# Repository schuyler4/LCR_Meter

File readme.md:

<h3> LCR Meter </h3>
<p>
 This is my attempt at making an LCR meter. It is still in progress, but here is a schematic if you are interested.
</p>
</img>
</img>

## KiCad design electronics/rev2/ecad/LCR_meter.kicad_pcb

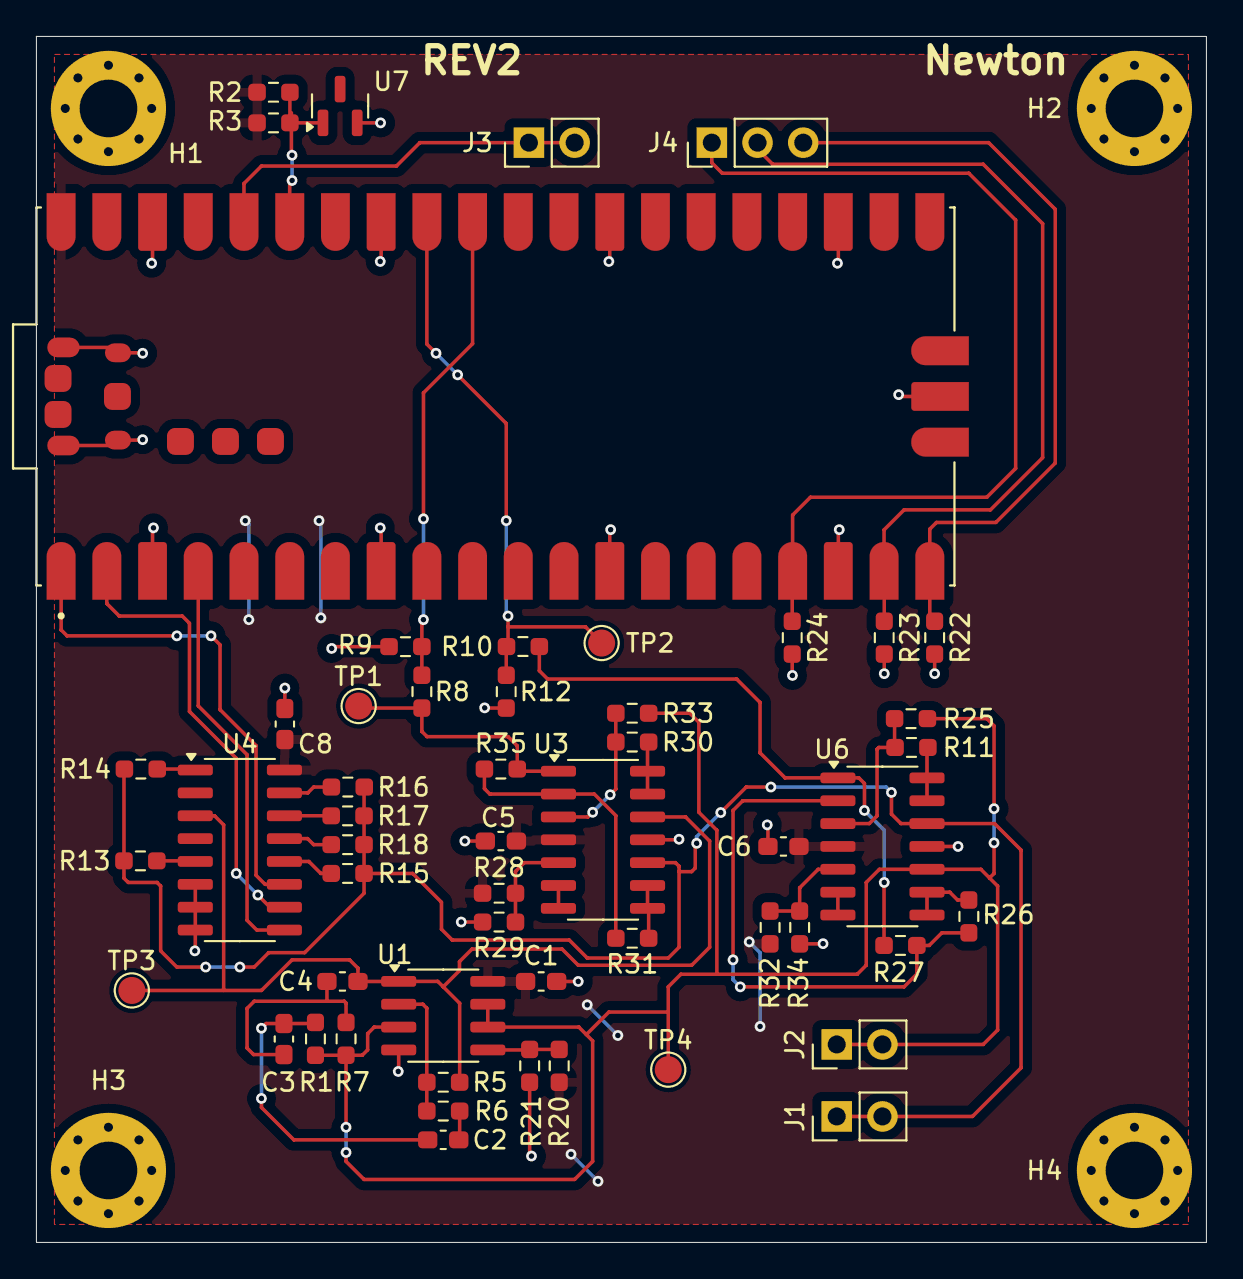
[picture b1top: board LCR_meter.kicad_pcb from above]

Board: 2 copper layers, 65.0 x 67.0 mm, 58 parts (0 on the bottom side), 40 nets.

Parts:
C1, C5, C6, C8: 0.1uF; C_0603_1608Metric_Pad1.08x0.95mm_HandSolder
C2, C3, C4: 100pF; C_0603_1608Metric_Pad1.08x0.95mm_HandSolder
H1, H2, H3, H4: M3; MountingHole_3.2mm_M3_Pad_Via
J1, J2: DUT; PinHeader_1x02_P2.54mm_Vertical
J3: SWITCH; PinHeader_1x02_P2.54mm_Vertical
J4: INPUT SWITCH; PinHeader_1x03_P2.54mm_Vertical
R1, R6, R7: 6.49k+/-0.1%; R_0603_1608Metric_Pad0.98x0.95mm_HandSolder
R2, R3, R22, R23, R24, R28, R29, R32, R34: 10k; R_0603_1608Metric_Pad0.98x0.95mm_HandSolder
R5: 249k+/-0.1%; R_0603_1608Metric_Pad0.98x0.95mm_HandSolder
R8, R10: 6.81k+/-0.1%; R_0603_1608Metric_Pad0.98x0.95mm_HandSolder
R9, R11, R12, R20, R21, R25, R26, R27, R30, R31, R33, R35: 10k+/-0.1%; R_0603_1608Metric_Pad0.98x0.95mm_HandSolder
R13: 49.9M+/-0.1%; R_0603_1608Metric_Pad0.98x0.95mm_HandSolder
R14: 4.99M+/-0.1%; R_0603_1608Metric_Pad0.98x0.95mm_HandSolder
R15: 499k+/-0.1%; R_0603_1608Metric_Pad0.98x0.95mm_HandSolder
R16: 49.9k+/-0.1%; R_0603_1608Metric_Pad0.98x0.95mm_HandSolder
R17: 4.99k+/-0.1%; R_0603_1608Metric_Pad0.98x0.95mm_HandSolder
R18: 499+/-0.1%; R_0603_1608Metric_Pad0.98x0.95mm_HandSolder
TP1, TP2, TP3, TP4: TestPoint_Pad_D1.5mm
U1: MCP6002-xSN; SOIC-8_3.9x4.9mm_P1.27mm
U3, U6: LM6144xIx; SOIC-14_3.9x8.7mm_P1.27mm
U4: 74HC4051; SOIC-16_3.9x9.9mm_P1.27mm
U5: SC0915; MODULE_SC0915
U7: LM4040DBZ-3; SOT-23

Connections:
+3.3V: J3.1, J3.2, U5.36 (3V3_OUT)
+5V: C1.1, C5.1, C6.1, C8.2, R2.1, R3.1, R20.1, R28.1, R32.1, U1.8 (V+), U3.4 (V+), U4.16 (VCC), U5.40 (VBUS), U6.4 (V+)
/DiffAmp1/IN+: C4.2, R5.2, TP3.1, U1.1, U3.12 (+), U4.3 (A)
/DiffAmp1/IN-: J1.1, J1.2, R13.2, R14.2, R15.2, R16.2, R17.2, R18.2, U3.10 (+), U6.12 (+)
/DiffAmp1/OUT: R8.2, R35.2, TP1.1, U3.1
/DiffAmp1/REF: J2.1, J2.2, R1.2, R7.2, R25.1, R33.1, TP4.1, U1.3 (+), U1.6 (-), U1.7, U6.10 (+)
/DiffAmp2/OUT: R10.2, R27.2, U6.1
/bit0: U4.11 (S0), U5.1 (GP0)
/bit1: U4.10 (S1), U5.2 (GP1)
/bit2: U4.9 (S2), U5.4 (GP2)
GND: C1.2, C5.2, C6.2, C8.1, H1.1, H2.1, H3.1, H4.1, R9.1, R12.2, R21.2, R22.2, R23.2, R24.2, R29.2, R34.2, U1.4 (V-), U3.11 (V-), U4.6 (~E), U4.7 (VEE), U4.8 (GND), U5.3 (GND), U5.8 (GND), U5.13 (GND), U5.18 (GND), U5.23 (GND), U5.28 (GND), U5.33 (AGND), U5.38 (GND), U5.A (USB_SHIELD), U5.B (USB_SHIELD), U5.C (USB_SHIELD), U5.D (USB_SHIELD), U5.D2 (GND), U6.11 (V-), U7.2 (A)
unnamed: C2.1, R6.2
unnamed: C2.2, C3.1, R1.1
unnamed: C3.2, C4.1, R7.1
unnamed: J4.1, R24.1, U5.17 (GP13)
unnamed: J4.2, R23.1, U5.19 (GP14)
unnamed: J4.3, R22.1, U5.20 (GP15)
unnamed: R5.1, R6.1, U1.2 (-)
unnamed: R20.2, R21.1, U1.5 (+)
unnamed: R30.2, R33.2, U3.3 (+)
unnamed: R31.2, R35.1, U3.2 (-)
unnamed: R28.2, R29.1, U3.5 (+)
unnamed: U3.6 (-), U3.7
unnamed: R31.1, U3.8, U3.9 (-)
unnamed: R30.1, U3.13 (-), U3.14
unnamed: R18.1, U4.13 (A0)
unnamed: R17.1, U4.14 (A1)
unnamed: R16.1, U4.15 (A2)
unnamed: R15.1, U4.12 (A3)
unnamed: R14.1, U4.1 (A4)
unnamed: R13.1, U4.5 (A5)
unnamed: R2.2, R3.2, U5.35 (ADC_VREF), U7.1 (K)
unnamed: R8.1, R9.2, U5.31 (GP26)
unnamed: R10.1, R12.1, TP2.1, U5.32 (GP27)
unnamed: R11.2, R25.2, U6.3 (+)
unnamed: R26.2, R27.1, U6.2 (-)
unnamed: R32.2, R34.1, U6.5 (+)
unnamed: U6.6 (-), U6.7
unnamed: R26.1, U6.8, U6.9 (-)
unnamed: R11.1, U6.13 (-), U6.14

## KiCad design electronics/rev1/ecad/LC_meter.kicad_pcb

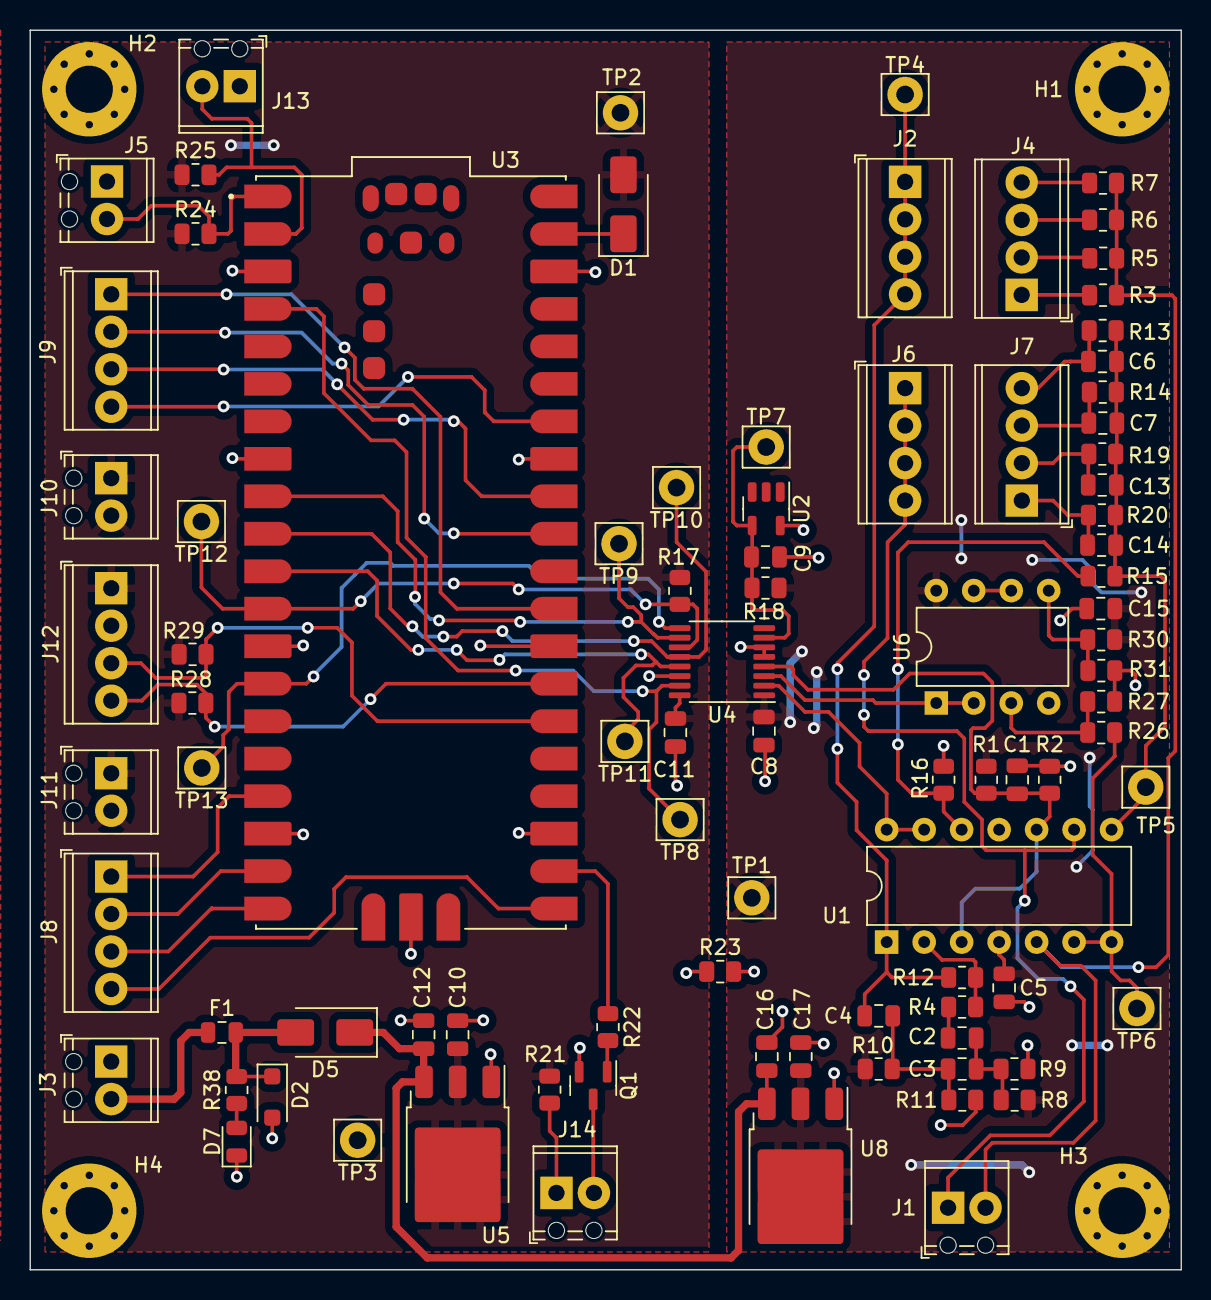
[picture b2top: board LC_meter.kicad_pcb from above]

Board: 2 copper layers, 78.0 x 84.0 mm, 93 parts (0 on the bottom side), 56 nets.

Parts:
C1, C5, C8, C11, C15, C16: 0.1uF; C_0805_2012Metric
C2, C3, C4: 100pF; C_0805_2012Metric
C6, C7, C13, C14: PNU; C_0805_2012Metric
C9, C10, C12, C17: 10uF; C_0805_2012Metric
D1, D5: B140-13-F; D_SMA
D2: SMF13A; D_SOD-123F
D7: LTST-C171TBKT; LED_0805_2012Metric
F1: 2A; Fuse_0805_2012Metric
H1, H2, H3, H4: M3; MountingHole_3.2mm_M3_Pad_Via
J1: DUT; TerminalBlock_Phoenix_MPT-0,5-2-2.54_1x02_P2.54mm_Horizontal
J2, J4, J6, J7: Switch; TerminalBlock_Phoenix_MPT-0,5-4-2.54_1x04_P2.54mm_Horizontal
J3: 12V Power; TerminalBlock_Phoenix_MPT-0,5-2-2.54_1x02_P2.54mm_Horizontal
J5, J13: Mode Switch; TerminalBlock_Phoenix_MPT-0,5-2-2.54_1x02_P2.54mm_Horizontal
J8: Thevenin Range Switch Indicator; TerminalBlock_Phoenix_MPT-0,5-4-2.54_1x04_P2.54mm_Horizontal
J9: Current Range Switch Indicator; TerminalBlock_Phoenix_MPT-0,5-4-2.54_1x04_P2.54mm_Horizontal
J10, J11: Range Switch; TerminalBlock_Phoenix_MPT-0,5-2-2.54_1x02_P2.54mm_Horizontal
J12: Display Connector; TerminalBlock_Phoenix_MPT-0,5-4-2.54_1x04_P2.54mm_Horizontal
J14: Panel LED; TerminalBlock_Phoenix_MPT-0,5-2-2.54_1x02_P2.54mm_Horizontal
Q1: 2N7002; SOT-23
R1, R2, R16, R27: 10k+/-0.1%; R_0805_2012Metric
R3: 499+/-0.1%; R_0805_2012Metric
R4: 6.49k; R_0805_2012Metric
R5: 4.99k+/-0.1%; R_0805_2012Metric
R6: 49.9k+/-0.1%; R_0805_2012Metric
R7: 499k+/-0.1%; R_0805_2012Metric
R8, R9, R10, R11: 13k; R_0805_2012Metric
R12: 187k; R_0805_2012Metric
R13: 249+/-0.1%; R_0805_2012Metric
R14: 2.49k+/-0.1%; R_0805_2012Metric
R15, R26: 2.21k+/-0.1%; R_0805_2012Metric
R17, R24, R25, R28, R29, R30, R31: 10k; R_0805_2012Metric
R18, R22: 1k; R_0805_2012Metric
R19, R20: PNU; R_0805_2012Metric
R21: 68; R_0805_2012Metric
R23: 0; R_0805_2012Metric
R38: 1.78k; R_0805_2012Metric
TP1, TP2, TP3, TP4, TP5, TP6, TP7, TP8, TP9, TP10, TP11, TP12, TP13: 4952; Pin_D1.2mm_L10.2mm_W2.9mm_FlatFork
U1: LM6144xIx; DIP-14_W7.62mm
U2: LM4030-4.096; SOT-23-5
U3: Raspberry Pi Pico SC0915; MODULE_SC0915
U4: ADS8328IPW; TSSOP-16_4.4x5mm_P0.65mm
U5: LM1117DT-3.3; TO-252-3_TabPin2
U6: LM6142xIx; DIP-8_W7.62mm
U8: LM1117DT-5.0; TO-252-3_TabPin2

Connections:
+3.3V: C10.1, C11.1, D1.2 (A), J10.1, J10.2, J11.1, J11.2, J12.1, R17.1, R21.1, R24.1, R25.1, R28.1, R29.1, TP2.1, U4.16 (+VBD), U5.2 (VO)
+5V: C5.1, C8.1, C15.1, C17.1, R1.1, R8.2, R10.2, R18.1, R30.1, TP1.1, U1.4 (V+), U4.1 (+VA), U6.8 (V+), U8.2 (VO)
+12V: F1.1, J3.2
/Analog Front End/CONVST: TP13.1, U3.14 (GP10), U4.9 (CONVST)
/Analog Front End/CS: R17.2, TP12.1, U3.12 (GP9), U4.11 (FS/CS)
/Analog Front End/DATA_IN: TP10.1, U3.10 (GP7), U4.12 (SDI)
/Analog Front End/DATA_OUT: TP11.1, U3.11 (GP8), U4.13 (SDO)
/Analog Front End/INTERUPT: TP9.1, U3.9 (GP6), U4.10 (EOC/INT)
/Analog Front End/SCK: TP8.1, U3.4 (GP2), U4.15 (SCLK)
/Analog Front End/V/2: C1.1, R1.2, R2.1, U1.3 (+), U1.10 (+), U4.4 (COM)
/SCL: J12.4, R28.2, U3.27 (GP21)
/SDA: J12.3, R29.2, U3.26 (GP20)
GNDA: C1.2, C5.2, C8.2, C9.2, C15.2, C16.2, C17.2, H1.1, H3.1, R2.2, R9.2, R11.2, R16.2, R23.2, R27.2, R31.1, U1.11 (V-), U2.5 (A), U4.5 (AGND), U4.6 (REF-), U6.4 (V-), U8.1 (GND)
GNDD: C10.2, C11.2, C12.2, D2.2 (A), D7.1 (K), H2.1, H4.1, J3.1, J5.1, J12.2, J13.1, Q1.2 (S), R23.1, TP3.1, U3.3 (GND), U3.8 (GND), U3.13 (GND), U3.18 (GND), U3.23 (GND), U3.28 (GND), U3.33 (AGND), U3.38 (GND), U3.D2 (GND), U4.14 (BDGND), U5.1 (GND)
unnamed: C2.1, C3.2, R8.1, R9.1
unnamed: C2.2, R4.1
unnamed: C3.1, C4.2, R10.1, R11.1
unnamed: C6.2, C7.2, C13.2, C14.2, R13.2, R14.2, R15.2, R19.2, R20.2, TP5.1, U1.8
unnamed: D1.1 (K), U3.39 (VSYS)
unnamed: D2.1 (K), D5.2 (A), F1.2, R38.2
unnamed: C12.1, C16.1, D5.1 (K), U5.3 (VI), U8.3 (VI)
unnamed: D7.2 (A), R38.1
unnamed: J1.1, J6.1, J6.2, J6.3, J6.4, U1.9 (-)
unnamed: J1.2, R3.2, R5.2, R6.2, R7.2, U1.5 (+)
unnamed: C4.1, J2.1, J2.2, J2.3, J2.4, R12.2, TP4.1, U1.1
unnamed: J4.1, R3.1
unnamed: J4.2, R5.1
unnamed: J4.3, R6.1
unnamed: J4.4, R7.1
unnamed: J5.2, R24.2, U3.1 (GP0)
unnamed: C14.1, J7.1, R20.1
unnamed: C13.1, J7.2, R19.1
unnamed: C7.1, J7.3, R14.1
unnamed: C6.1, J7.4, R13.1
unnamed: J8.1, U3.17 (GP13)
unnamed: J8.2, U3.19 (GP14)
unnamed: J8.3, U3.20 (GP15)
unnamed: J8.4, U3.21 (GP16)
unnamed: J9.1, U3.29 (GP22)
unnamed: J9.2, U3.31 (GP26)
unnamed: J9.3, U3.32 (GP27)
unnamed: J9.4, U3.34 (GP28)
unnamed: J13.2, R25.2, U3.2 (GP1)
unnamed: J14.1, R21.2
unnamed: J14.2, Q1.3 (D)
unnamed: Q1.1 (G), R22.2
unnamed: R4.2, R12.1, U1.2 (-)
unnamed: R26.2, TP6.1, U1.6 (-), U1.7
unnamed: R15.1, R16.1, U1.12 (+)
unnamed: U1.13 (-), U1.14, U4.2 (+IN1)
unnamed: C9.1, R18.2, TP7.1, U2.4 (K), U4.7 (REF+)
unnamed: R22.1, U3.22 (GP17)
unnamed: U4.3 (+IN0), U6.1, U6.2 (-)
unnamed: R26.1, R27.1, U6.3 (+)
unnamed: R30.2, R31.2, U6.5 (+)
unnamed: U6.6 (-), U6.7

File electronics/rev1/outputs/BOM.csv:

Item,Qty,Reference(s),Value,Distributor,Distributor Part #,Part #,Unit Price,Price,Carted
1,6,"C1, C5, C8, C11, C15, C16",0.1uF,DIGIKEY,1276-1003-1-ND,CL21B104KBCNNNC,0.1,0.6,T
2,3,"C2, C3, C4",100pF,DIGIKEY,1276-1261-1-ND,CL21C101JCANNNC,0.1,0.3,T
3,4,"C6, C7, C13, C14",PNU,N/A,N/A,N/A,0,0,
4,4,"C9, C10, C12, C17",10uF,DIGIKEY,1276-1096-1-ND,CL21A106KOQNNNE,0.1,0.4,T
5,2,"D1, D5",B140-13-F,DIGIKEY,B140-FDICT-ND,B140-13-F,0.39,0.78,T
6,1,D2,SMF13A,DIGIKEY,SMF13A-TPMSCT-ND,SMF13A-TP,0.38,0.38,T
7,1,D7,LTST-C171TBKT,DIGIKEY,160-1645-1-ND,LTST-C171TBKT,0.32,0.32,T
8,1,F1,2A,DIGIKEY,2315-FCC20202AATPCT-ND,FCC20202AATP,0.1,0.1,T
9,4,"H1, H2, H3, H4",M3,N/A,N/A,N/A,0,0,
10,1,J1,DUT,DIGIKEY,ED10561-ND,OSTVN02A150,1.08,1.08,T
11,4,"J2, J4, J6, J7",Switch,DIGIKEY,ED10563-ND,OSTVN04A150,1.64,6.56,T
12,1,J3,12V Power,DIGIKEY,ED10561-ND,OSTVN02A150,1.08,1.08,T
13,2,"J5, J13",Mode Switch,DIGIKEY,ED10561-ND,OSTVN02A150,1.08,2.16,T
14,1,J8,Thevenin Range Switch Indicator,DIGIKEY,ED10563-ND,OSTVN04A150,1.64,1.64,T
15,1,J9,Current Range Switch Indicator,DIGIKEY,ED10563-ND,OSTVN04A150,1.64,1.64,T
16,2,"J10, J11",Range Switch,DIGIKEY,ED10561-ND,OSTVN02A150,1.08,2.16,T
17,1,J12,Display Connector,DIGIKEY,ED10563-ND,OSTVN04A150,1.64,1.64,T
18,1,J14,Panel LED,DIGIKEY,ED10561-ND,OSTVN02A150,1.08,1.08,T
19,1,Q1,2N7002,DIGIKEY,2N7002NCT-ND,2N7002,0.45,0.45,T
20,4,"R1, R2, R16, R27",10k+/-0.1%,DIGIKEY,P10KDACT-ND,ERA-6AEB103V,0.32,1.28,T
21,1,R3,499+/-0.1%,DIGIKEY,RG20P499BCT-ND,RG2012P-4990-B-T5,0.48,0.48,T
22,1,R4,6.49k,DIGIKEY,RMCF0805FT6K49CT-ND,RMCF0805FT6K49,0.1,0.1,T
23,1,R5,4.99k+/-0.1%,DIGIKEY,P4.99KDACT-ND,ERA-6AEB4991V,0.32,0.32,T
24,1,R6,49.9k+/-0.1%,DIGIKEY,P49.9KDACT-ND,ERA-6AEB4992V,0.32,0.32,T
25,1,R7,499k+/-0.1%,DIGIKEY,RG20P499KBCT-ND,RG2012P-4993-B-T5,0.48,0.48,T
26,4,"R8, R9, R10, R11",13k,DIGIKEY,RMCF0805FT13K0CT-ND,RMCF0805FT13K0,0.1,0.4,T
27,1,R12,187k,DIGIKEY,738-RMCF0805FT187KCT-ND,RMCF0805FT187K,0.1,0.1,T
28,1,R13,249+/-0.1%,DIGIKEY,P20523CT-ND,ERJ-PB6B2490V,0.37,0.37,T
29,1,R14,2.49k+/-0.1%,DIGIKEY,13-RP0805BRD072K49LCT-ND,RP0805BRD072K49L,0.48,0.48,T
30,2,"R15, R26",2.21k+/-0.1%,DIGIKEY,P2.21KDACT-ND,ERA-6AEB2211V,0.32,0.64,T
31,7,"R17, R24, R25, R28, R29, R30, R31",10k,DIGIKEY,RMCF0805FT10K0CT-ND,RMCF0805FT10K0,0.1,0.7,T
32,2,"R18, R22",1k,DIGIKEY,RMCF0805FT1K00CT-ND,RMCF0805FT1K00,0.1,0.2,T
33,2,"R19, R20",PNU,N/A,N/A,N/A,0,0,
34,1,R21,68,DIGIKEY,P68DACT-ND,ERA-6AEB680V,0.32,0.32,T
35,1,R23,0,DIGIKEY,RMCF0805ZT0R00CT-ND,RMCF0805ZT0R00,0.1,0.1,T
36,1,R38,1.78k,DIGIKEY,YAG4850CT-ND,RT0805BRD071K78L,0.36,0.36,T
37,13,"TP1, TP2, TP3, TP4, TP5, TP6, TP7, TP8, TP9, TP10, TP11, TP12, TP13",4952,DIGIKEY,36-4952-ND,4952,0.26,3.38,T
38,1,U1,LM6144xIx,DIGIKEY,LM6144BIN/NOPB-ND,LM6144BIN/NOPB,9.01,9.01,T
39,1,U2,LM4030-4.096,DIGIKEY,296-41427-1-ND,LM4030CMF-4.096/NOPB,1.7,1.7,T
40,1,U3,Raspberry Pi Pico SC0915,DIGIKEY,2648-SC0915CT-ND,SC0915,4,4,INVENTORY
41,1,U4,ADS8328IPW,DIGIKEY,296-19766-ND,ADS8328IPW,14.78,14.78,T
42,1,U5,LM1117DT-3.3,DIGIKEY,LM1117DT-3.3/NOPB-ND,LM1117DT-3.3/NOPB,1.81,1.81,T
43,1,U6,LM6142xIx,MOUSER,926-LM6142BIN/NOPB ,LM6142BIN/NOPB ,5.58,5.58,
44,1,U8,LM1117DT-5.0,DIGIKEY,LM1117DT-5.0/NOPB-ND,LM1117DT-5.0/NOPB,1.81,1.81,T
Total,,,,,,,,71.09,

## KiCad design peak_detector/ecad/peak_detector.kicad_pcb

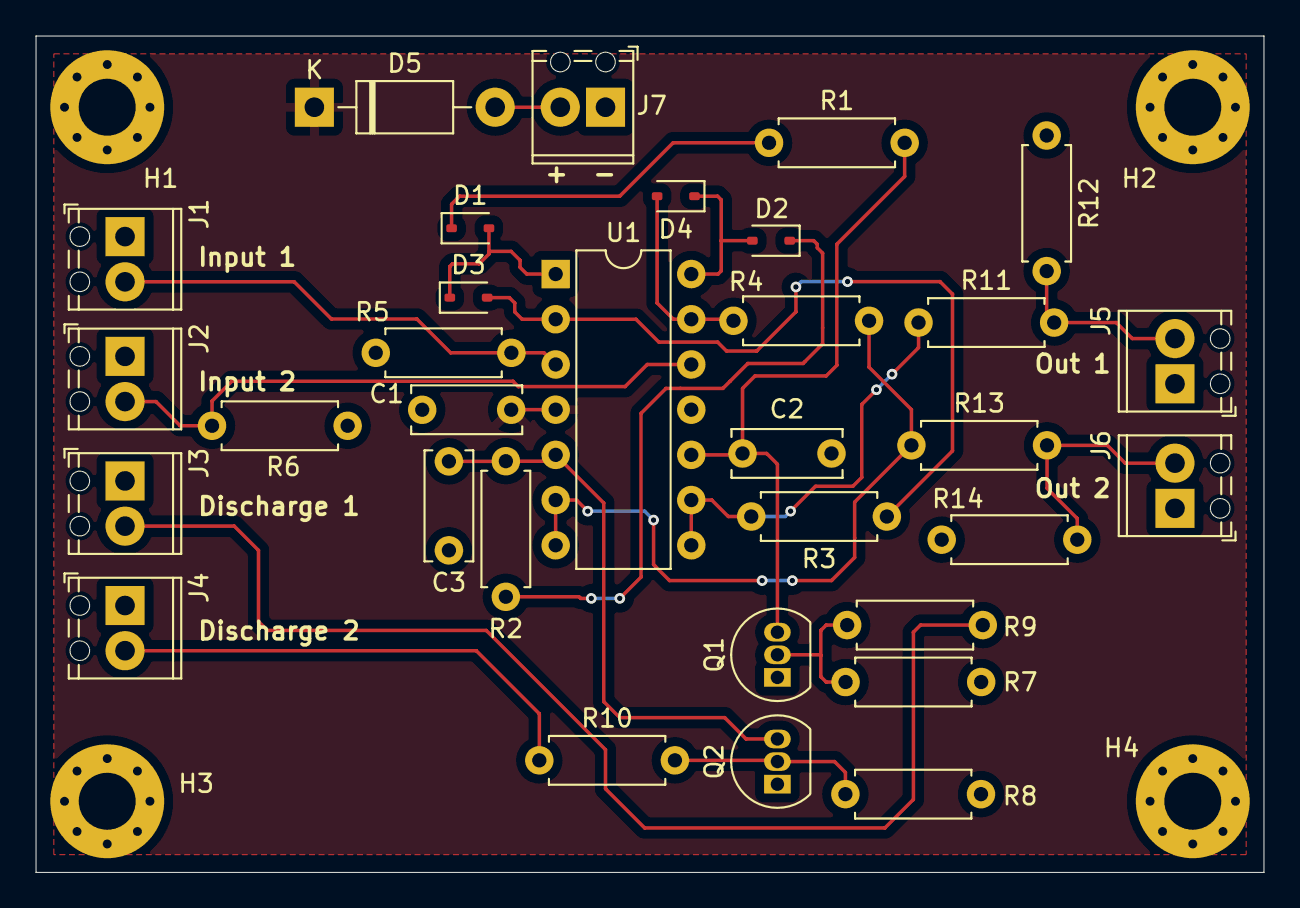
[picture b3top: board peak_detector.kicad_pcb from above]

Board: 2 copper layers, 69.0 x 47.0 mm, 36 parts (0 on the bottom side), 21 nets.

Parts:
C1: 0.1uF; C_Disc_D6.0mm_W2.5mm_P5.00mm
C2, C3: 0.47uF; C_Disc_D6.0mm_W2.5mm_P5.00mm
D1, D2, D3, D4: CMDD6001; D_SOD-323
D5: 1N5817; D_DO-41_SOD81_P10.16mm_Horizontal
H1, H2, H3, H4: M3; MountingHole_3.2mm_M3_Pad_Via
J1: Input 1; TerminalBlock_Phoenix_MPT-0,5-2-2.54_1x02_P2.54mm_Horizontal
J2: Input 2; TerminalBlock_Phoenix_MPT-0,5-2-2.54_1x02_P2.54mm_Horizontal
J3: Discharge 1; TerminalBlock_Phoenix_MPT-0,5-2-2.54_1x02_P2.54mm_Horizontal
J4: Discharge 2; TerminalBlock_Phoenix_MPT-0,5-2-2.54_1x02_P2.54mm_Horizontal
J5: Out 1; TerminalBlock_Phoenix_MPT-0,5-2-2.54_1x02_P2.54mm_Horizontal
J6: Out 2; TerminalBlock_Phoenix_MPT-0,5-2-2.54_1x02_P2.54mm_Horizontal
J7: Power; TerminalBlock_Phoenix_MPT-0,5-2-2.54_1x02_P2.54mm_Horizontal
Q1, Q2: 2N7000; TO-92_Inline
R1, R2: 100; R_Axial_DIN0207_L6.3mm_D2.5mm_P7.62mm_Horizontal
R3, R4, R9, R10, R12, R14: 1k; R_Axial_DIN0207_L6.3mm_D2.5mm_P7.62mm_Horizontal
R5, R6: 100k; R_Axial_DIN0207_L6.3mm_D2.5mm_P7.62mm_Horizontal
R7, R8: 10k; R_Axial_DIN0207_L6.3mm_D2.5mm_P7.62mm_Horizontal
R11, R13: 221; R_Axial_DIN0207_L6.3mm_D2.5mm_P7.62mm_Horizontal
U1: MCP6024; DIP-14_W7.62mm

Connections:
+5V: C1.1, D5.1 (K), U1.4 (V+)
GND: C1.2, C2.2, C3.2, H1.1, H2.1, H3.1, H4.1, J1.1, J2.1, J3.1, J4.1, J5.1, J6.1, J7.1, Q1.1 (S), Q2.1 (S), R5.2, R6.2, R7.2, R8.2, R12.1, R14.1, U1.11 (V-)
unnamed: D1.2 (A), D3.1 (K), U1.1
unnamed: D1.1 (K), R1.1
unnamed: D2.2 (A), D4.1 (K), U1.14
unnamed: D2.1 (K), R2.1
unnamed: D3.2 (A), R3.1, U1.2 (-)
unnamed: D4.2 (A), R4.1, U1.13 (-)
unnamed: D5.2 (A), J7.2
unnamed: J1.2, R5.1, U1.3 (+)
unnamed: J2.2, R6.1, U1.12 (+)
unnamed: J3.2, R9.1
unnamed: J4.2, R10.1
unnamed: J5.2, R11.2, R12.2
unnamed: J6.2, R13.2, R14.2
unnamed: C2.1, Q1.3 (D), R1.2, U1.10 (+)
unnamed: Q1.2 (G), R7.1, R9.2
unnamed: C3.1, Q2.3 (D), R2.2, U1.5 (+)
unnamed: Q2.2 (G), R8.1, R10.2
unnamed: R4.2, R13.1, U1.6 (-), U1.7
unnamed: R3.2, R11.1, U1.8, U1.9 (-)

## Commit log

2023-11-01 the start of some firmware
2023-11-18 new computer
2023-11-21 schematic work
2023-11-24 switch to time based
2023-11-28 time stuff
2023-12-03 auto balancing
2023-12-08 ok range calcs and schematic
2023-12-12 crashed
2023-12-12 fished crash
2023-12-13 layout
2023-12-14 stability
2023-12-14 more layout
2023-12-14 remove lck files
2023-12-14 remvoe lck files
2023-12-16 general work
2023-12-19 layout draft
2023-12-20 more work on algorithm
2023-12-21 finished algorithm
2023-12-22 boms
2023-12-28 firmware talking
2023-12-29 ADC Driver Work
2023-12-30 firmware work
2023-12-31 C component calcs
2024-01-01 fixed calc bug
2024-01-01 removed file
2024-01-02 BOM update
2024-01-02 firmware and BOM
2024-01-03 display driver
2024-01-07 display counting
2024-01-08 added license and readme
2024-01-21 ordered parts
2024-02-08 spi stuff
2024-02-09 more spi stuff
2024-05-13 peak detector work
2024-09-07 varius work
2024-09-08 started rev2 compatible with voltpeek
2024-09-10 rev2 work
2024-09-10 clean up
2024-09-10 schematic is back
2024-09-17 schematic rev2 might be done
2024-09-23 rev2 design work
2024-10-07 preliminary sampling tests
2024-10-08 not working
2024-10-08 crap
2024-10-09 getting some readings that make sense
2024-10-09 minor change
2024-10-10 implemented some stuff
2024-10-11 ranging work
2024-10-12 more ranging stuff
2024-10-13 reading impedances
2024-10-16 stray capacitance problem
2024-10-17 cal expierment
